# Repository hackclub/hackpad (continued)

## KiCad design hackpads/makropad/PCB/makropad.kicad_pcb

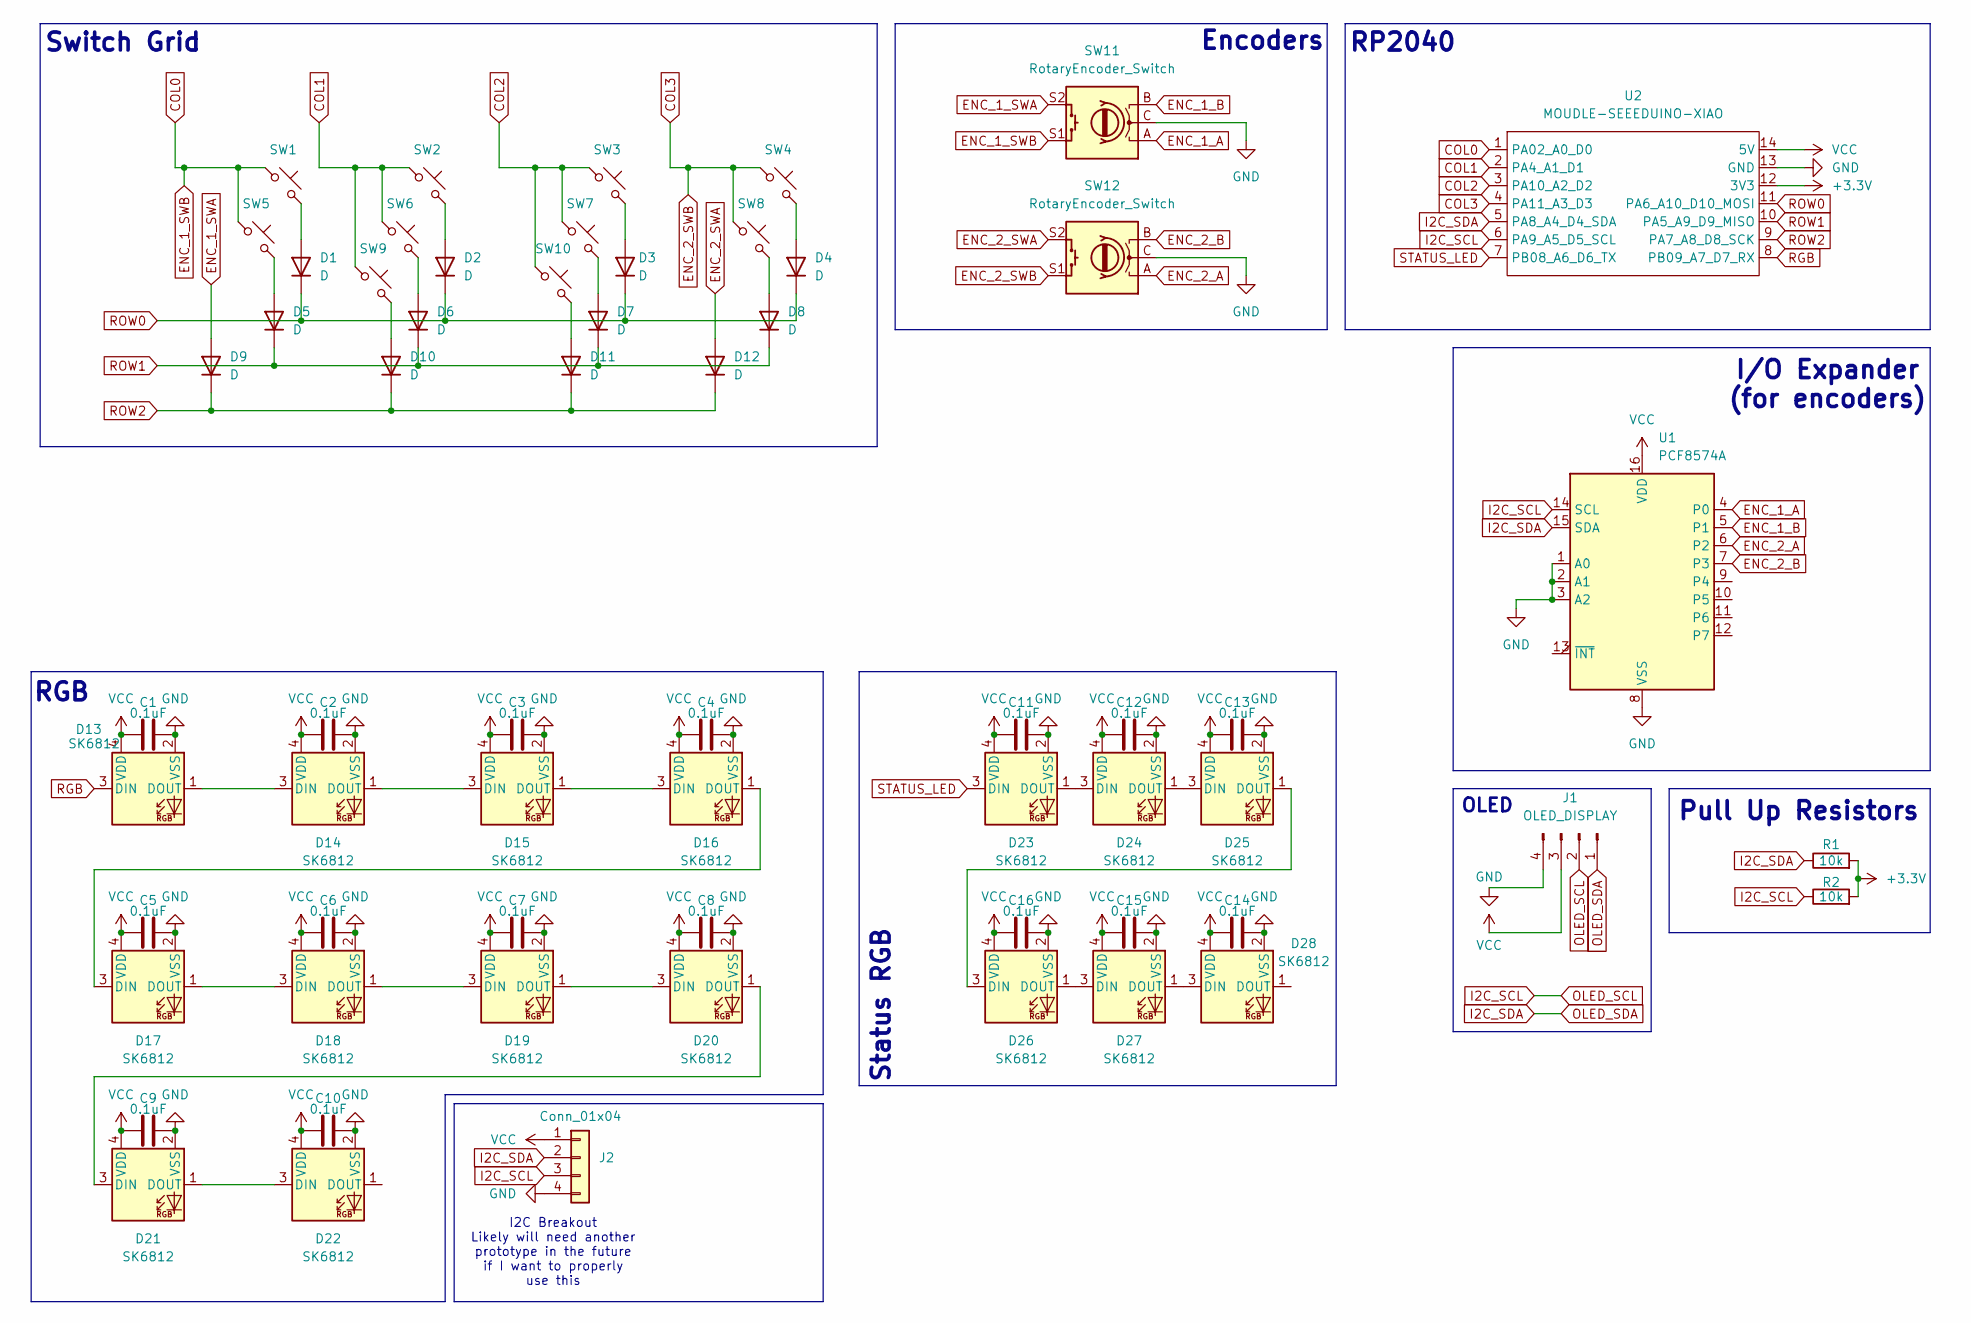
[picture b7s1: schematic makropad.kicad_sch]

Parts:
C1, C2, C3, C4, C5, C6, C7, C8, C9, C10, C11, C12, C13, C14, C15, C16: 0.1uF; C_1206_3216Metric
D1, D2, D3, D4, D5, D6, D7, D8, D9, D10, D11, D12: D; D_SOD-123
D13, D14, D15, D16, D17, D18, D19, D20, D21, D22: SK6812; SK6812MINI-E
D23, D24, D25, D26, D27, D28: SK6812; LED_SK6812MINI_PLCC4_3.5x3.5mm_P1.75mm
J1: OLED_DISPLAY; SSD1306-0.91-OLED-4pin-128x32
J2: Conn_01x04; 4pin
R1, R2: 10k; R_1206_3216Metric
SW1, SW2, SW3, SW4, SW5, SW6, SW7, SW8, SW9, SW10: SW_Push_45deg; SW_Kailh_Choc_V2
SW11, SW12: RotaryEncoder_Switch; encoder
U1: PCF8574A; SOIC127P1032X265-16N
U2: MOUDLE-SEEEDUINO-XIAO; XIAO-Generic-Hybrid-14P-2.54-21X17.8MM

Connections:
+3.3V: R1.2, R2.2, U2.12 (3V3)
COL0: SW1.1, SW5.1, SW11.S1, U2.1 (PA02_A0_D0)
COL1: SW2.1, SW6.1, SW9.1, U2.2 (PA4_A1_D1)
COL2: SW3.1, SW7.1, SW10.1, U2.3 (PA10_A2_D2)
COL3: SW4.1, SW8.1, SW12.S1, U2.4 (PA11_A3_D3)
ENC_1_A: SW11.A, U1.4 (P0)
ENC_1_B: SW11.B, U1.5 (P1)
ENC_1_SWA: D9.2 (A), SW11.S2
ENC_2_A: SW12.A, U1.6 (P2)
ENC_2_B: SW12.B, U1.7 (P3)
ENC_2_SWA: D12.2 (A), SW12.S2
GND: C1.2, C2.2, C3.2, C4.2, C5.2, C6.2, C7.2, C8.2, C9.2, C10.2, C11.2, C12.2, C13.2, C14.2, C15.2, C16.2, D13.2 (VSS), D14.2 (VSS), D15.2 (VSS), D16.2 (VSS), D17.2 (VSS), D18.2 (VSS), D19.2 (VSS), D20.2 (VSS), D21.2 (VSS), D22.2 (VSS), D23.2 (VSS), D24.2 (VSS), D25.2 (VSS), D26.2 (VSS), D27.2 (VSS), D28.2 (VSS), J1.4, J2.4, SW11.C, SW12.C, U1.1 (A0), U1.2 (A1), U1.3 (A2), U1.8 (VSS), U2.13 (GND)
I2C_SCL: J1.2, J2.3, R2.1, U1.14 (SCL), U2.6 (PA9_A5_D5_SCL)
I2C_SDA: J1.1, J2.2, R1.1, U1.15 (SDA), U2.5 (PA8_A4_D4_SDA)
unnamed: D1.2 (A), SW1.2
unnamed: D2.2 (A), SW2.2
unnamed: D3.2 (A), SW3.2
unnamed: D4.2 (A), SW4.2
unnamed: D5.2 (A), SW5.2
unnamed: D6.2 (A), SW6.2
unnamed: D7.2 (A), SW7.2
unnamed: D8.2 (A), SW8.2
unnamed: D10.2 (A), SW9.2
unnamed: D11.2 (A), SW10.2
unnamed: D13.1 (DOUT), D14.3 (DIN)
unnamed: D14.1 (DOUT), D15.3 (DIN)
unnamed: D15.1 (DOUT), D16.3 (DIN)
unnamed: D16.1 (DOUT), D17.3 (DIN)
unnamed: D17.1 (DOUT), D18.3 (DIN)
unnamed: D18.1 (DOUT), D19.3 (DIN)
unnamed: D19.1 (DOUT), D20.3 (DIN)
unnamed: D20.1 (DOUT), D21.3 (DIN)
unnamed: D21.1 (DOUT), D22.3 (DIN)
unnamed: D23.1 (DOUT), D24.3 (DIN)
unnamed: D24.1 (DOUT), D25.3 (DIN)
unnamed: D25.1 (DOUT), D26.3 (DIN)
unnamed: D26.1 (DOUT), D27.3 (DIN)
unnamed: D27.1 (DOUT), D28.3 (DIN)
RGB: D13.3 (DIN), U2.8 (PB09_A7_D7_RX)
ROW0: D1.1 (K), D2.1 (K), D3.1 (K), D4.1 (K), U2.11 (PA6_A10_D10_MOSI)
ROW1: D5.1 (K), D6.1 (K), D7.1 (K), D8.1 (K), U2.10 (PA5_A9_D9_MISO)
ROW2: D9.1 (K), D10.1 (K), D11.1 (K), D12.1 (K), U2.9 (PA7_A8_D8_SCK)
STATUS_LED: D23.3 (DIN), U2.7 (PB08_A6_D6_TX)
VCC: C1.1, C2.1, C3.1, C4.1, C5.1, C6.1, C7.1, C8.1, C9.1, C10.1, C11.1, C12.1, C13.1, C14.1, C15.1, C16.1, D13.4 (VDD), D14.4 (VDD), D15.4 (VDD), D16.4 (VDD), D17.4 (VDD), D18.4 (VDD), D19.4 (VDD), D20.4 (VDD), D21.4 (VDD), D22.4 (VDD), D23.4 (VDD), D24.4 (VDD), D25.4 (VDD), D26.4 (VDD), D27.4 (VDD), D28.4 (VDD), J1.3, J2.1, U1.16 (VDD), U2.14 (5V)

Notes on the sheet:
RGB
Switch Grid
RP2040
OLED
I2C Breakout Likely will need another prototype in the future if I want to properly use this
Encoders
Status RGB
I/O Expander (for encoders)
Pull Up Resistors

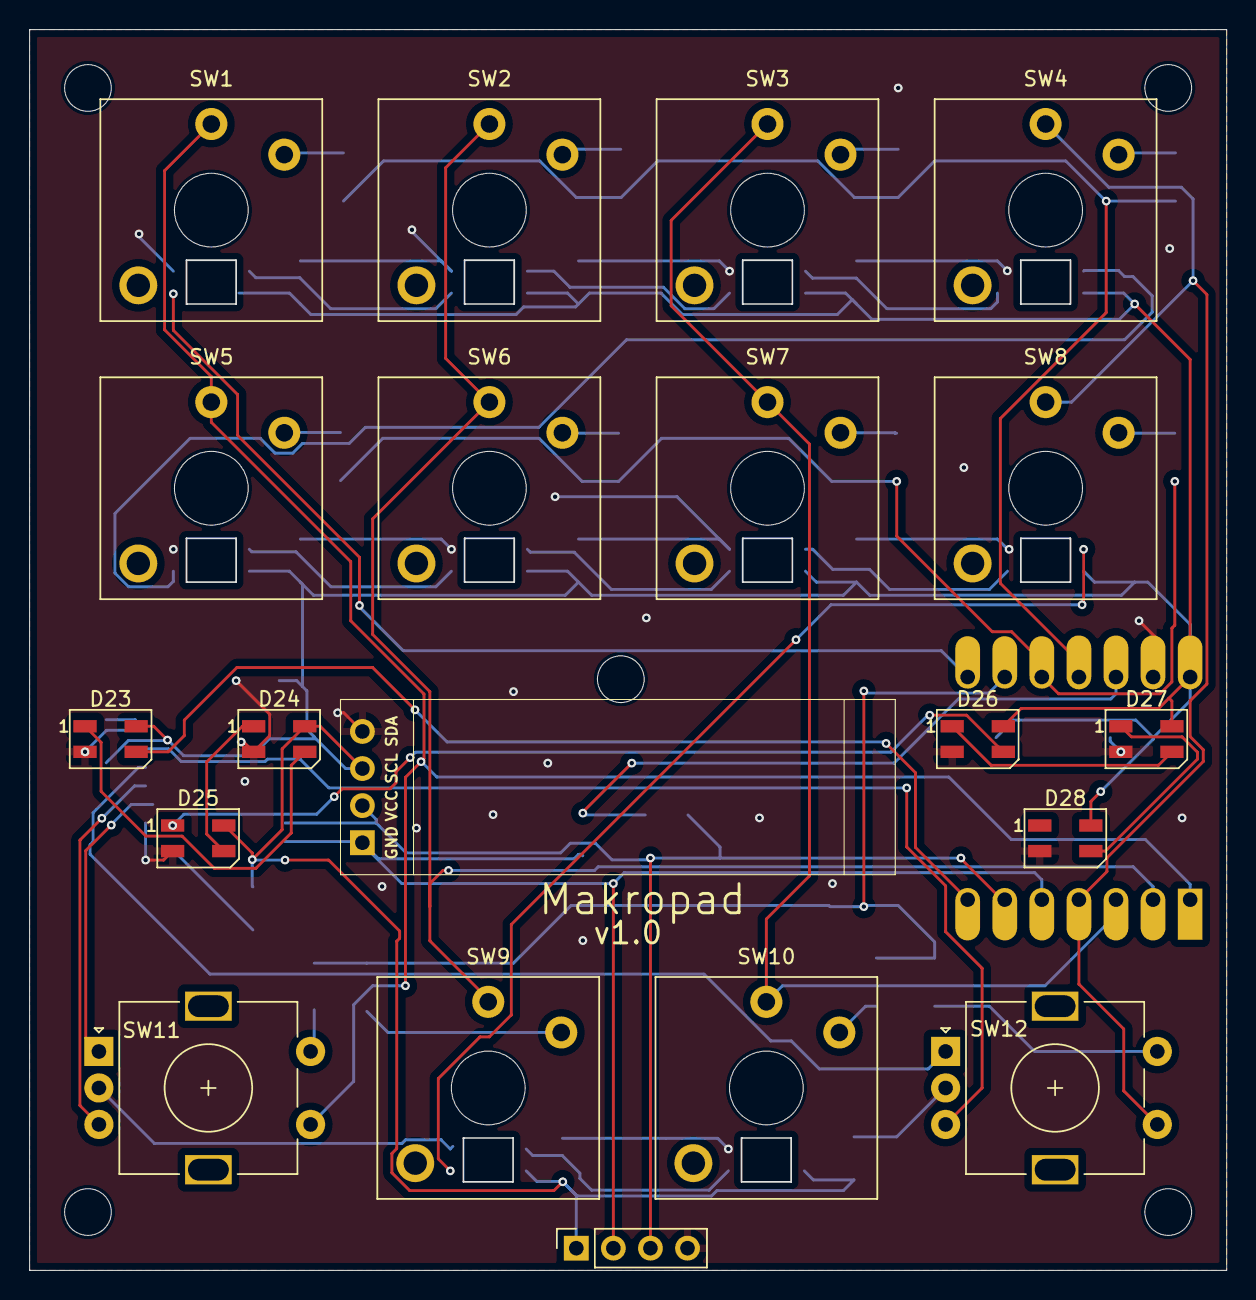
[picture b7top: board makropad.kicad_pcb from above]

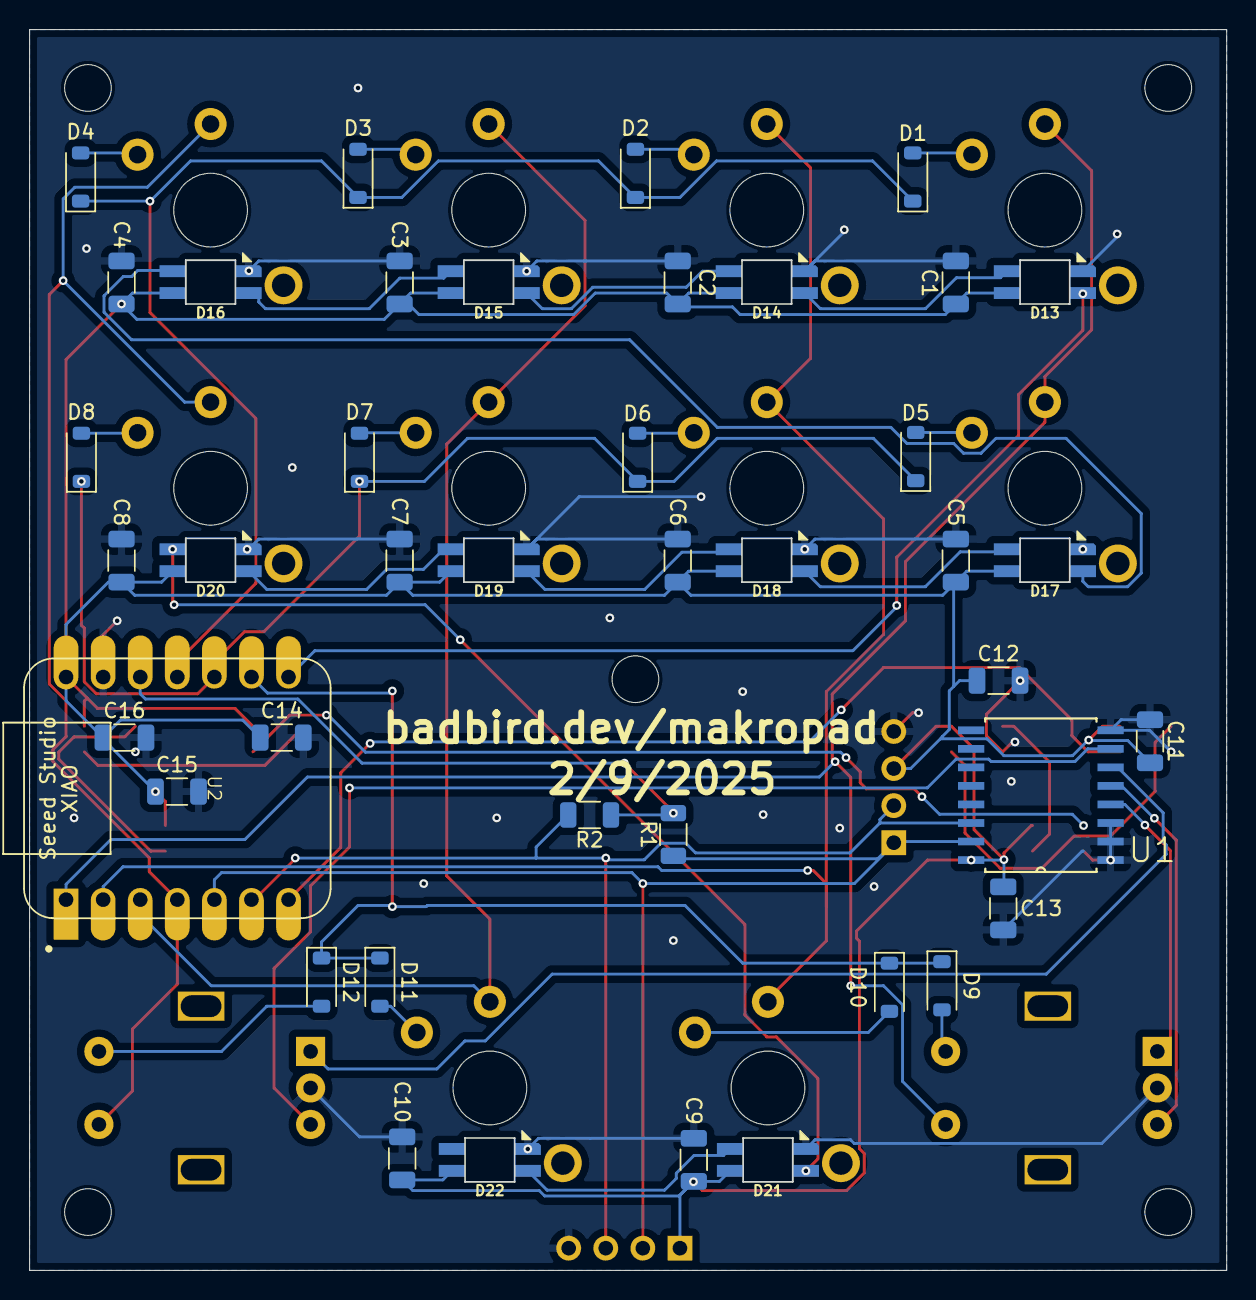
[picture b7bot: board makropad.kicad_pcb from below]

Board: 2 copper layers, 82.0 x 85.0 mm, 67 parts (43 on the bottom side), 44 nets.

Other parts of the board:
MH1, MH2, MH3, MH4, MH5: MountingHole_3.2mm_M3
